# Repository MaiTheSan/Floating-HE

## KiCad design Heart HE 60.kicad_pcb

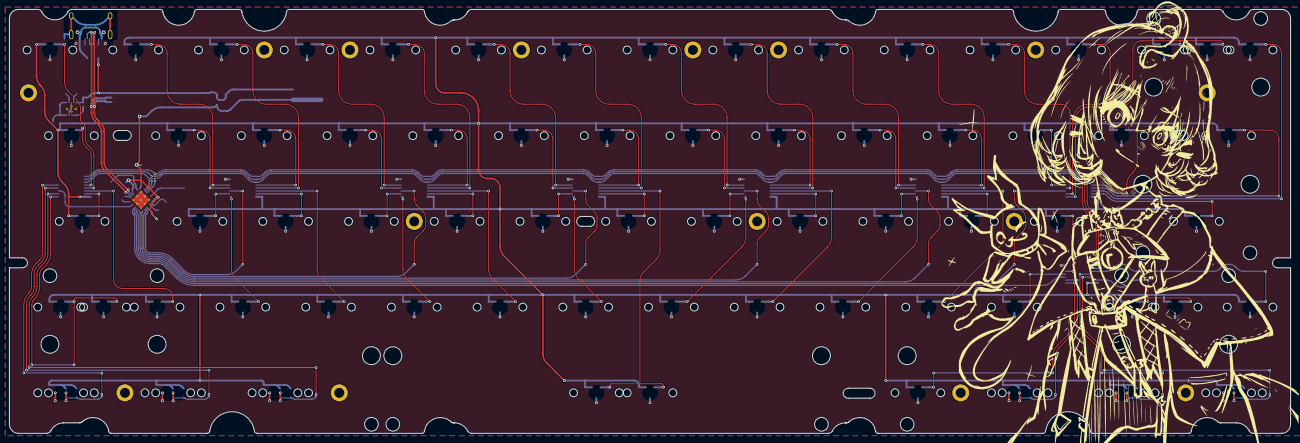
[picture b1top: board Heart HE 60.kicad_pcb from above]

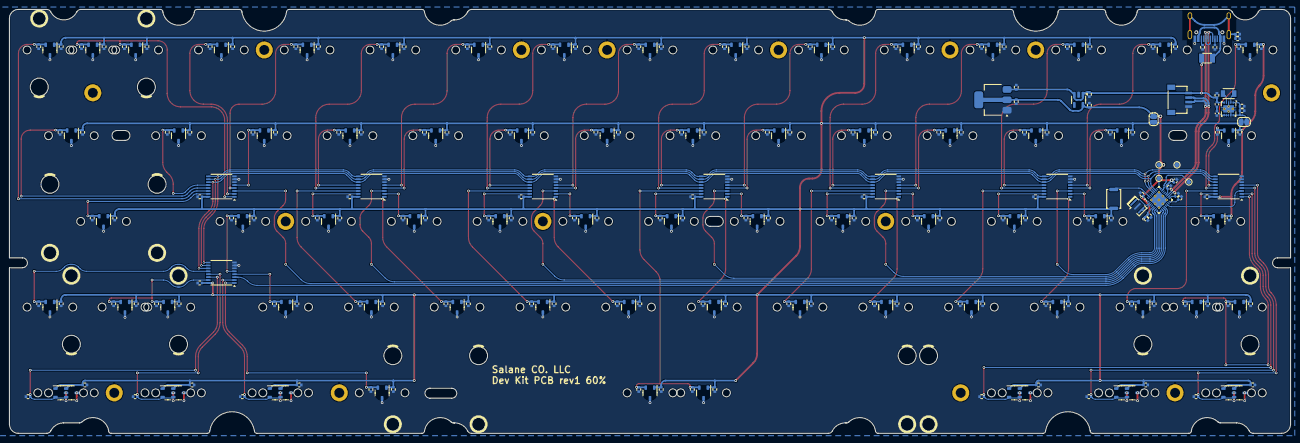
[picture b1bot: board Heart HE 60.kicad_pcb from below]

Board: 2 copper layers, 284.7 x 94.2 mm, 277 parts (262 on the bottom side), 94 nets.

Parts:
C1, C2, C4, C5, C6, C9, C10, C13, C27, C33, C38, C39, C44, C45, C50, C51, C56, C57, C63, C68, C69, C74, C75, C76, C77, C78, C80, C81, C82, C83, C84, C85, C87, C91, C92, C93, C96, C97, C99, C101, C102, C105, C111, C112, C113, C114, C115, C117, C119, C120, C121, C122, C123, C124, C125, C126, C127, C128, C129, C130, C131, C132, C133, C134, C135, C136, C137, C138, C139, C140, C141, C142, C143, C144, C146, C147, C148, C149, C151, C152, C153, C154, C155, C157, C158, C159, C160, C163: 0.1uF; C_0402
C7, C14, C20, C21, C25, C26, C32: 10uF; C_0402
C8: 4.7uF; C_0402
C11: 1uF; C_0402
C15, C16, C17, C18, C19, C22, C23, C24, C28, C29, C30, C31, C34, C35, C36, C37, C40, C41, C42, C43, C46, C47, C48, C49, C52, C53, C54, C55, C58, C59, C60, C61, C64, C65, C66, C67, C70, C71, C72, C73, C79, C88, C89, C90, C94, C95, C100, C107, C108, C156, C168, C169, C170, C171, C172, C173, C175, C176, C177, C178: 4.7nF; C_0402
C165: 0.1uF; C_0402_1005Metric
F1: 1A; Fuse_SMD1206_Reflow
H3, H4, H5, H6, H7, H8, H9, H10, H11, H12, H13, H14, H15, H17, H18: MountingHole; MountingHole_2.2mm_M2_DIN965_Pad
J2: Conn_01x04; JST-SR-4
JP1, JP2: Jumper_2_Bridged; SolderJumper-2_P1.3mm_Open_RoundedPad1.0x1.5mm
L1: 2.2uH; L_TDK_NLV25_2.5x2.0mm
R1: 1M; R_0402
R2, R3: 5.1k; R_0402
R30: 10k; R_0402
R35: 12k; R_0402
R113: 100R; R_0402_1005Metric
SW1: SW_Push; SW_Push_SPST_NO_Alps_SKRK
TP1, TP2, TP3, TP4: TestPoint; TestPoint_Pad_D1.0mm
U2, U32, U38, U45, U51, U56, U62, U69: 74HC4051; SSOP-16_4.4x5.2mm_P0.65mm
U3: SLSS49E-3; SLSS49E_MX_2U
U4, U6, U8, U68: SLSS49E-3; SLSS49E_MX_1.5U_Rotate
U5, U39: SLSS49E-3; SLSS49E_MX_1U_Rotate
U7: SLSS49E-3; SLSS49E_MX_7U-ReversedStabilizers
U10, U16, U17, U18, U22, U23, U24, U25, U28, U29, U30, U31, U34, U35, U36, U37, U40, U41, U42, U43, U46, U47, U48, U49, U52, U53, U54, U55, U58, U59, U60, U61, U64, U65, U66, U67, U70, U71, U72, U73, U76, U77, U78, U79, U80, U82, U83, U88, U94, U97: SLSS49E-3; SLSS49E_MX_1U
U11, U89: SLSS49E-3; SLSS49E_MX_1.5U
U12, U91: SLSS49E-3; SLSS49E_MX_1.75U
U14, U20, U21, U26, U50, U74: SLSS49E-3; SLSS49E_MX_1.25U_Rotate
U15, U75: SLSS49E-3; SLSS49E_MX_1.25U
U19: AP2112K-3.3; SOT-23-5
U27: AT32F405KxU7-4; QFN-32-1EP_4x4mm_P0.4mm_EP2.9x2.9mm_ThermalVias
U33: SLSS49E-3; SLSS49E_MX_2.25U
U44: SLSS49E-3; SLSS49E_MX_6.25U-ReversedStabilizers
U57: SLSS49E-3; SLSS49E_MX_2.75U
U63: AMS1117-3.3; SOT-223-3_TabPin2
U84: SLSS49E-3; SLSS49E_MX_2.25U-ReversedStabilizers
U85: TPS63001; Texas_DRC0010J_ThermalVias
USB1: HRO-TYPE-C-31-M-12; HRO-TYPE-C-31-M-12-Assembly
Y1: 12Mhz (15p); Resonator_SMD_Murata_CSTxExxV-3Pin_3.0x1.1mm

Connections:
00: C16.2, U2.13 (A0), U10.3
01: C22.2, U16.3, U32.5 (A5)
02: C28.2, U22.3, U32.13 (A0)
03: C34.2, U28.3, U38.5 (A5)
04: C40.2, U34.3, U38.13 (A0)
05: C46.2, U40.3, U45.5 (A5)
06: C52.2, U45.13 (A0), U46.3
07: C58.2, U51.5 (A5), U52.3
08: C64.2, U51.13 (A0), U58.3
09: C70.2, U56.5 (A5), U64.3
010: C76.2, U56.13 (A0), U70.3
10: C17.2, U2.12 (A3), U11.3
11: C23.2, U17.3, U32.4 (A7)
011: C82.2, U62.4 (A7), U76.3
12: C29.2, U23.3, U32.12 (A3)
012: C88.2, U62.2 (A6), U82.3
13: C35.2, U29.3, U38.4 (A7)
013: C15.2, C94.2, U3.3, U62.1 (A4), U88.3
14: C41.2, U35.3, U38.12 (A3)
014: C100.2, U62.14 (A1), U94.3
15: C47.2, U41.3, U45.4 (A7)
16: C53.2, U45.12 (A3), U47.3
17: C59.2, U51.4 (A7), U53.3
18: C65.2, U51.12 (A3), U59.3
19: C71.2, U56.4 (A7), U65.3
20: C18.2, U2.15 (A2), U12.3
21: C24.2, U18.3, U32.2 (A6)
22: C30.2, U24.3, U32.15 (A2)
23: C36.2, U30.3, U38.2 (A6)
24: C42.2, U36.3, U38.15 (A2)
25: C48.2, U42.3, U45.2 (A6)
26: C54.2, U45.15 (A2), U48.3
27: C60.2, U51.2 (A6), U54.3
28: C66.2, U51.15 (A2), U60.3
29: C72.2, U56.2 (A6), U66.3
30: C19.2, C168.2, U2.1 (A4), U33.3, U75.3
31: C31.2, U2.14 (A1), U80.3
32: C37.2, U25.3, U32.1 (A4)
33: C43.2, U31.3, U32.14 (A1)
34: C49.2, U37.3, U38.1 (A4)
35: C55.2, U38.14 (A1), U43.3
36: C61.2, U45.1 (A4), U49.3
37: C67.2, U51.1 (A4), U55.3
38: C73.2, U51.14 (A1), U61.3
39: C79.2, U56.1 (A4), U67.3
40: C169.2, U2.5 (A5), U4.3, U14.3
41: C170.2, U2.4 (A7), U5.3, U20.3
42: C171.2, U2.2 (A6), U6.3, U26.3
45: C177.2, C178.2, U7.3, U44.3, U45.14 (A1)
49: C175.2, U15.3, U69.1 (A4)
110: C77.2, U56.12 (A3), U71.3
111: C83.2, U62.5 (A5), U77.3
112: C89.2, U62.12 (A3), U83.3
113: C95.2, U62.13 (A0), U89.3
210: C78.2, U56.15 (A2), U72.3
211: C84.2, U69.5 (A5), U78.3
212: C90.2, U62.15 (A2), U84.3
310: C85.2, U56.14 (A1), U73.3
311: C97.2, U69.4 (A7), U79.3
313: C107.2, C156.2, U57.3, U69.15 (A2), U91.3
314: C108.2, U69.12 (A3), U97.3
410: C176.2, U8.3, U21.3, U69.2 (A6)
413: C172.2, U39.3, U50.3, U69.13 (A0)
414: C173.2, U68.3, U69.14 (A1), U74.3
+3.3VA: C2.2, C4.2, C5.2, C6.2, C8.2, C9.2, C10.2, C11.1, C13.1, C14.2, C20.2, C25.2, C27.2, C32.2, C33.2, C38.2, C39.2, C44.2, C45.2, C50.2, C51.2, C56.2, C57.2, C63.2, C68.2, C69.2, C74.2, C75.2, C80.2, C81.2, C87.2, C91.2, C92.2, C93.2, C96.2, C99.2, C101.2, C102.2, C105.2, C111.2, C112.2, C113.2, C114.2, C115.2, C117.2, C119.2, C120.2, C121.2, C122.2, C123.2, C124.2, C125.2, C126.2, C127.2, C128.2, C129.2, C130.2, C131.2, C132.2, C133.2, C134.2, C135.2, C136.2, C137.2, C138.2, C139.2, C140.2, C141.2, C142.2, C143.2, C144.2, C146.2, C147.2, C148.2, C149.2, C151.2, C152.2, C153.2, C154.2, C155.2, C157.2, C158.2, C159.2, C160.2, C163.2, JP1.1 (A), JP1.2 (B), JP2.1 (A), JP2.2 (B), SW1.2, TP2.1, U2.16 (VCC), U3.1 (+), U4.1 (+), U5.1 (+), U6.1 (+), U7.1 (+), U8.1 (+), U10.1 (+), U11.1 (+), U12.1 (+), U14.1 (+), U15.1 (+), U16.1 (+), U17.1 (+), U18.1 (+), U19.5 (VOUT), U20.1 (+), U21.1 (+), U22.1 (+), U23.1 (+), U24.1 (+), U25.1 (+), U26.1 (+), U27.1 (VDD), U27.5 (VDDA), U27.20 (VDD), U28.1 (+), U29.1 (+), U30.1 (+), U31.1 (+), U32.16 (VCC), U33.1 (+), U34.1 (+), U35.1 (+), U36.1 (+), U37.1 (+), U38.16 (VCC), U39.1 (+), U40.1 (+), U41.1 (+), U42.1 (+), U43.1 (+), U44.1 (+), U45.16 (VCC), U46.1 (+), U47.1 (+), U48.1 (+), U49.1 (+), U50.1 (+), U51.16 (VCC), U52.1 (+), U53.1 (+), U54.1 (+), U55.1 (+), U56.16 (VCC), U57.1 (+), U58.1 (+), U59.1 (+), U60.1 (+), U61.1 (+), U62.16 (VCC), U63.2 (VO), U64.1 (+), U65.1 (+), U66.1 (+), U67.1 (+), U68.1 (+), U69.16 (VCC), U70.1 (+), U71.1 (+), U72.1 (+), U73.1 (+), U74.1 (+), U75.1 (+), U76.1 (+), U77.1 (+), U78.1 (+), U79.1 (+), U80.1 (+), U82.1 (+), U83.1 (+), U84.1 (+), U85.1 (VOUT), U85.10 (FB), U88.1 (+), U89.1 (+), U91.1 (+), U94.1 (+), U97.1 (+)
+5V: C7.2, C21.2, C26.2, F1.2, J2.1, R113.1, U19.1 (VIN), U19.3 (EN), U63.3 (VI), U85.5 (VIN)
A0: U27.6 (PA0), U32.3 (A)
A1: U27.7 (PA1), U38.3 (A)
A2: U27.8 (PA2), U45.3 (A)
A3: U27.9 (PA3), U51.3 (A)
A4: U27.10 (PA4), U56.3 (A)
A5: U27.11 (PA5), U62.3 (A)
A6: U27.12 (PA6), U69.3 (A)
A8: U2.3 (A), U27.14 (PB0)
Boot0: SW1.1, U27.31 (PF11/BOOT0)
D+: J2.3, U27.19 (OTGHS_D+), USB1.6 (DP1), USB1.8 (DP2)
D-: J2.2, U27.18 (OTGHS_D-), USB1.5 (DN2), USB1.7 (DN1)
GND: C1.2, C2.1, C4.1, C5.1, C6.1, C7.1, C8.1, C9.1, C10.1, C11.2, C13.2, C14.1, C15.1, C16.1, C17.1, C18.1, C19.1, C20.1, C21.1, C22.1, C23.1, C24.1, C25.1, C26.1, C27.1, C28.1, C29.1, C30.1, C31.1, C32.1, C33.1, C34.1, C35.1, C36.1, C37.1, C38.1, C39.1, C40.1, C41.1, C42.1, C43.1, C44.1, C45.1, C46.1, C47.1, C48.1, C49.1, C50.1, C51.1, C52.1, C53.1, C54.1, C55.1, C56.1, C57.1, C58.1, C59.1, C60.1, C61.1, C63.1, C64.1, C65.1, C66.1, C67.1, C68.1, C69.1, C70.1, C71.1, C72.1, C73.1, C74.1, C75.1, C76.1, C77.1, C78.1, C79.1, C80.1, C81.1, C82.1, C83.1, C84.1, C85.1, C87.1, C88.1, C89.1, C90.1, C91.1, C92.1, C93.1, C94.1, C95.1, C96.1, C97.1, C99.1, C100.1, C101.1, C102.1, C105.1, C107.1, C108.1, C111.1, C112.1, C113.1, C114.1, C115.1, C117.1, C119.1, C120.1, C121.1, C122.1, C123.1, C124.1, C125.1, C126.1, C127.1, C128.1, C129.1, C130.1, C131.1, C132.1, C133.1, C134.1, C135.1, C136.1, C137.1, C138.1, C139.1, C140.1, C141.1, C142.1, C143.1, C144.1, C146.1, C147.1, C148.1, C149.1, C151.1, C152.1, C153.1, C154.1, C155.1, C156.1, C157.1, C158.1, C159.1, C160.1, C163.1, C165.1, C168.1, C169.1, C170.1, C171.1, C172.1, C173.1, C175.1, C176.1, C177.1, C178.1, J2.4, R1.2, R2.1, R3.1, R30.2, R35.2, TP1.1, U2.6 (~E), U2.7 (VEE), U2.8 (GND), U3.2 (-), U4.2 (-), U5.2 (-), U6.2 (-), U7.2 (-), U8.2 (-), U10.2 (-), U11.2 (-), U12.2 (-), U14.2 (-), U15.2 (-), U16.2 (-), U17.2 (-), U18.2 (-), U19.2 (GND), U20.2 (-), U21.2 (-), U22.2 (-), U23.2 (-), U24.2 (-), U25.2 (-), U26.2 (-), U27.33 (VSS/VSSA), U28.2 (-), U29.2 (-), U30.2 (-), U31.2 (-), U32.6 (~E), U32.7 (VEE), U32.8 (GND), U33.2 (-), U34.2 (-), U35.2 (-), U36.2 (-), U37.2 (-), U38.6 (~E), U38.7 (VEE), U38.8 (GND), U39.2 (-), U40.2 (-), U41.2 (-), U42.2 (-), U43.2 (-), U44.2 (-), U45.6 (~E), U45.7 (VEE), U45.8 (GND), U46.2 (-), U47.2 (-), U48.2 (-), U49.2 (-), U50.2 (-), U51.6 (~E), U51.7 (VEE), U51.8 (GND), U52.2 (-), U53.2 (-), U54.2 (-), U55.2 (-), U56.6 (~E), U56.7 (VEE), U56.8 (GND), U57.2 (-), U58.2 (-), U59.2 (-), U60.2 (-), U61.2 (-), U62.6 (~E), U62.7 (VEE), U62.8 (GND), U63.1 (GND), U64.2 (-), U65.2 (-), U66.2 (-), U67.2 (-), U68.2 (-), U69.6 (~E), U69.7 (VEE), U69.8 (GND), U70.2 (-), U71.2 (-), U72.2 (-), U73.2 (-), U74.2 (-), U75.2 (-), U76.2 (-), U77.2 (-), U78.2 (-), U79.2 (-), U80.2 (-), U82.2 (-), U83.2 (-), U84.2 (-), U85.3 (PGND), U85.9 (GND), U85.11 (PGND), U88.2 (-), U89.2 (-), U91.2 (-), U94.2 (-), U97.2 (-), USB1.1 (GND), USB1.12 (GND), Y1.2
unnamed: R35.1, U27.17 (OTGHS_R)
unnamed: R30.1, U27.16 (PB2)
unnamed: C165.2, R113.2, U85.6 (EN), U85.7 (PS/SYNC), U85.8 (VINA)
unnamed: L1.1, U85.4 (L1)
unnamed: L1.2, U85.2 (L2)
unnamed: R2.2, USB1.4 (CC1)
unnamed: R3.2, USB1.10 (CC2)
unnamed: C1.1, R1.1, USB1.13 (SHIELD)
S0: U2.11 (S0), U27.26 (PB3), U32.11 (S0), U38.11 (S0), U45.11 (S0), U51.11 (S0), U56.11 (S0), U62.11 (S0), U69.11 (S0)
S1: U2.10 (S1), U27.27 (PB4), U32.10 (S1), U38.10 (S1), U45.10 (S1), U51.10 (S1), U56.10 (S1), U62.10 (S1), U69.10 (S1)
S2: U2.9 (S2), U27.28 (PB5), U32.9 (S2), U38.9 (S2), U45.9 (S2), U51.9 (S2), U56.9 (S2), U62.9 (S2), U69.9 (S2)
VCC: F1.1, USB1.2 (VBUS), USB1.11 (VBUS)
XTAL_IN: U27.2 (PF0), Y1.1
XTAL_OUT: U27.3 (PF1), Y1.3
p23: TP3.1, U27.23 (PA13)
p24: TP4.1, U27.24 (PA14)

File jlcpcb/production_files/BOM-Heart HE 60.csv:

Comment,Designator,Footprint,LCSC,Quantity
0.1uF,"C1,C10,C100,C101,C102,C105,C107,C108,C111,C112,C113,C114,C115,C117,C119,C120,C121,C122,C123,C124,C125,C126,C127,C128,C129,C13,C130,C131,C132,C133,C134,C135,C136,C137,C138,C139,C140,C141,C142,C143,C144,C146,C147,C148,C149,C15,C151,C152,C153,C154,C155,C156,C157,C158,C159,C16,C160,C163,C165,C168,C169,C17,C170,C171,C172,C173,C175,C176,C177,C178,C18,C19,C2,C22,C23,C24,C27,C28,C29,C30,C31,C33,C34,C35,C36,C37,C38,C39,C4,C40,C41,C42,C43,C44,C45,C46,C47,C48,C49,C5,C50,C51,C52,C53,C54,C55,C56,C57,C58,C59,C6,C60,C61,C63,C64,C65,C66,C67,C68,C69,C70,C71,C72,C73,C74,C75,C76,C77,C78,C79,C80,C81,C82,C83,C84,C85,C87,C88,C89,C9,C90,C91,C92,C93,C94,C95,C96,C97,C99",C_0402,C1525,149
10uF,"C14,C20,C21,C25,C26,C32,C7",C_0402,C15525,7
HRO-TYPE-C-31-M-12,USB1,HRO-TYPE-C-31-M-12-Assembly,C165948,1
4.7uF,C8,C_0402,C23733,1
100R,R113,R_0402_1005Metric,C25076,1
10k,R30,R_0402,C25744,1
12k,R35,R_0402,C25752,1
5.1k,"R2,R3",R_0402,C25905,2
1M,R1,R_0402,C26083,1
TPS63001,U85,Texas_DRC0010J_ThermalVias,C28060,1
SLSS49E-3,"U10,U11,U12,U14,U15,U16,U17,U18,U20,U21,U22,U23,U24,U25,U26,U28,U29,U3,U30,U31,U33,U34,U35,U36,U37,U39,U4,U40,U41,U42,U43,U44,U46,U47,U48,U49,U5,U50,U52,U53,U54,U55,U57,U58,U59,U6,U60,U61,U64,U65,U66,U67,U68,U7,U70,U71,U72,U73,U74,U75,U76,U77,U78,U79,U8,U80,U82,U83,U84,U88,U89,U91,U94,U97",SLSS49E_MX_1U,C2977713,74
2.2uH,L1,L_TDK_NLV25_2.5x2.0mm,C3040393,1
12Mhz (15p),Y1,Resonator_SMD_Murata_CSTxExxV-3Pin_3.0x1.1mm,C341520,1
1uF,C11,C_0402,C52923,1
74HC4051,"U2,U32,U38,U45,U51,U56,U62,U69",SSOP-16_4.4x5.2mm_P0.65mm,C5645,8
AMS1117-3.3,U63,SOT-223-3_TabPin2,C6186,1
SW_Push,SW1,SW_Push_SPST_NO_Alps_SKRK,,1
AT32F405KxU7-4,U27,QFN-32-1EP_4x4mm_P0.4mm_EP2.9x2.9mm_ThermalVias,,1
Conn_01x04,J2,JST-SR-4,,1
AP2112K-3.3,U19,SOT-23-5,,1
1A,F1,Fuse_SMD1206_Reflow,,1

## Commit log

2024-11-16 Upload file
2024-11-16 Refactor
2024-11-16 Remove production
2024-11-16 Change
2024-11-17 JLC part add and backup
2024-11-17 Add maping Component
2024-11-17 add remember comment
2024-11-20 JLC update
2024-11-20 Fix Component order part overwrite
2024-11-21 Make it 60%
2024-11-22 add production
2024-11-22 fix outline
2024-11-22 Final trace
2024-11-22 visual fix
2024-11-22 Trace fix
2024-11-22 PWR FIX
2024-11-22 Silk fix
2024-12-08 Edit outline.dxf
2024-12-11 small fix
